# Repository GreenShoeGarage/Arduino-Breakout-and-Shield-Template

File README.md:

# Arduino MKR and UNO R4 breakout boards and prototyping shields

Seven PCB designs, including the UNO R4 Minima riser, from Green Shoe Garage cover two Arduino families. Each family includes a base board, a prototyping shield with a solder grid, and a blank shield for custom components. Each base board brings Arduino pins out to headers and 2.54 mm screw terminals. Both shield variants plug into the headers on their matching base board.

| Family | Base board | Prototyping shield | Blank workspace shield |
| --- | --- | --- | --- |
| Arduino MKR | [MKR Terminal Carrier](boards/mkr/terminal-carrier/) breaks out the two 14-pin rows, using the MKR WiFi 1010 as its reference. | [MKR Carrier ProtoShield](boards/mkr/protoshield/) has a 7 × 25 prototyping grid. Its underside sockets J1 and J2 mate with carrier headers J3 and J4, respectively. | [MKR Blank Shield](boards/mkr/blank-shield/) leaves the center open for component footprints and routing. It retains the two 14-pin underside sockets and two M3 mounting holes. |
| Arduino UNO R4 | [UNO R4 Bench Breakout](boards/uno-r4/bench-breakout/) Rev B picks up standard headers and ICSP, plus ESP, Qwiic and OFF/RTC on WiFi or SWD on Minima through a [rigid riser](boards/uno-r4/minima-swd-riser/). | [UNO R4 Companion Shield](boards/uno-r4/companion-shield/) has underside sockets for the breakout headers, labeled solder rows, and a 12 × 15 prototyping grid. | [UNO R4 Blank Shield](boards/uno-r4/blank-shield/) leaves the prototyping area open for component footprints and routing. It retains the nine underside socket banks and their labeled solder rows. |

## UNO R4 direct-stack revision B

[Assembly guide (PDF)](boards/uno-r4/bench-breakout/drawings/UNO-R4-Direct-Assembly.pdf) · [Variant BOM](boards/uno-r4/bench-breakout/Assembly-BOM.csv) · [Flux project ZIPs](boards/uno-r4/flux-import/)

The WiFi carrier uses two underside sockets and three spring probes. The Minima carrier uses a soldered SWD riser. Assemble one variant per carrier. Both upper shields receive signals through the existing nine male/female header pairs. The enclosure uses two precision locating spacers.

## Open a board

Download or clone the repository. In KiCad 9, open the `.kicad_pro` file in the chosen board directory, then launch the Schematic Editor or PCB Editor from the project window. Keep the whole directory together when copying a board or packaging it individually. The symbol and footprint tables resolve paths relative to the project.

Flux users can import an individual UNO project from the linked ZIP folder using **Import → Project**. Each ZIP contains one schematic and one routed layout. Live Flux import remains untested.

All three MKR projects and both UNO R4 shield projects include local STEP models. The UNO R4 Bench Breakout references the standard KiCad 9 model library through `KICAD9_3DMODEL_DIR` for its 3D view.

## View PCB files on GitHub

Gerber Viewer for GitHub adds an interactive preview above GitHub's file content. It supports this repository's native KiCad PCB and schematic files through the embedded KiCanvas viewer.

1. Install and enable the Chrome extension. [Gerber Viewer for GitHub](https://chromewebstore.google.com/detail/gerber-viewer-for-github/kjempphffigplmkbpjamikbfgpmdfbfn)
2. Open this repository on GitHub in that browser, then select a PCB or schematic link below to visit its file page.
3. Use the embedded viewer to zoom and pan. For PCB layouts, toggle layers to inspect copper routing, silkscreen, and the board outline.

For a new GitHub repository, upload or commit the extracted project folders so each PCB and schematic has its own file page.

| Board | PCB layout | Schematic |
| --- | --- | --- |
| MKR Terminal Carrier | [View PCB](boards/mkr/terminal-carrier/MKR-Terminal-Carrier.kicad_pcb) | [View schematic](boards/mkr/terminal-carrier/MKR-Terminal-Carrier.kicad_sch) |
| MKR Carrier ProtoShield | [View PCB](boards/mkr/protoshield/MKR-Carrier-ProtoShield.kicad_pcb) | [View schematic](boards/mkr/protoshield/MKR-Carrier-ProtoShield.kicad_sch) |
| MKR Blank Shield | [View PCB](boards/mkr/blank-shield/MKR-Blank-Shield.kicad_pcb) | [View schematic](boards/mkr/blank-shield/MKR-Blank-Shield.kicad_sch) |
| UNO R4 Bench Breakout | [View PCB](boards/uno-r4/bench-breakout/UNO-R4-Breakout.kicad_pcb) | [View schematic](boards/uno-r4/bench-breakout/UNO-R4-Breakout.kicad_sch) |
| UNO R4 Companion Shield | [View PCB](boards/uno-r4/companion-shield/UNO-R4-Companion-Shield.kicad_pcb) | [View schematic](boards/uno-r4/companion-shield/UNO-R4-Companion-Shield.kicad_sch) |
| UNO R4 Blank Shield | [View PCB](boards/uno-r4/blank-shield/UNO-R4-Blank-Shield.kicad_pcb) | [View schematic](boards/uno-r4/blank-shield/UNO-R4-Blank-Shield.kicad_sch) |
| UNO R4 Minima SWD riser | [View PCB](boards/uno-r4/minima-swd-riser/UNO-R4-SWD-Riser.kicad_pcb) | [View schematic](boards/uno-r4/minima-swd-riser/UNO-R4-SWD-Riser.kicad_sch) |

The extension also previews Gerber and Excellon drill files, folders containing Gerber layers, and ZIP archives containing Gerber layers committed to GitHub.

## Routing verification

The UNO R4 Rev B verification covers the new carrier, the Minima riser and both mating shields. The November 26 verification package covers the three MKR Rev A boards. The reports record digital routing, rule, and pin-mapping checks. Physical assemblies await bench measurement.

| Family | Verification report | Continuity checklist | Complete verification package |
| --- | --- | --- | --- |
| MKR | [Routing verification (PDF)](boards/mkr/verification/MKR-Routing-Verification.pdf) | [Pin continuity (CSV)](boards/mkr/verification/MKR-Pin-Continuity.csv) | [Reports, netlists, and audit](boards/mkr/verification/) |
| UNO R4 | [Routing verification](boards/uno-r4/verification/README.md) | [Pin continuity (CSV)](boards/uno-r4/verification/UNO-R4-Direct-Continuity.csv) | [Evidence, audited inputs, and replay scripts](boards/uno-r4/verification/) |

Each UNO R4 board directory contains Gerber and drill files under `fabrication/`. The UNO R4 verification directory includes a replay for the copper, drill and assembled pin mappings. The previous cable-based design is archived in [Rev A history](boards/uno-r4/history/UNO-R4-Rev-A.zip).

## Board gallery

The PCB images below were regenerated from the current KiCad files on November 27, 2026. Layouts show front copper in red and back copper in blue. Select a 3D view or PCB layout to open the full-size image.

### Arduino MKR

| Board | 3D view | PCB layout |
| --- | --- | --- |
| [MKR Terminal Carrier](boards/mkr/terminal-carrier/) |  |  |
| [MKR Carrier ProtoShield](boards/mkr/protoshield/) |  |  |
| [MKR Blank Shield](boards/mkr/blank-shield/) |  |  |

<details>
<summary>MKR Blank Shield layout with a 20 mm scale bar</summary>

</details>

### Arduino UNO R4

| Board | 3D view | PCB layout |
| --- | --- | --- |
| [UNO R4 Bench Breakout](boards/uno-r4/bench-breakout/) |  |  |
| [UNO R4 Companion Shield](boards/uno-r4/companion-shield/) |  |  |
| [UNO R4 Blank Shield](boards/uno-r4/blank-shield/) |  |  |
| [UNO R4 Minima SWD riser](boards/uno-r4/minima-swd-riser/) |  |  |

## Stack enclosures

Both enclosures accept the prototyping shield or blank shield for their matching board family. The dimensions below are nominal. Both designs await a physical fit test.

| MKR stack enclosure | UNO R4 stack enclosure |
| --- | --- |
|  |  |
| **98 × 130 × 37.2 mm.** Print the base and one lid. The access lid exposes the prototyping area. The covered lid shelters it. | **132 × 120 × 43 mm.** Use the base, open bezel, and two precision locators with the Rev B assembly. |
| [Printable STLs](enclosures/mkr/fabrication/) · [Assembly guide (PDF)](enclosures/mkr/drawings/MKR-Stack-Assembly-Guide.pdf) · [CAD and source](enclosures/mkr/) | [Printable STLs](enclosures/uno-r4/fabrication/) · [Assembly guide (PDF)](enclosures/uno-r4/drawings/UNO-R4-Stack-Assembly.pdf) · [CAD and source](enclosures/uno-r4/) |

## Source and licenses

The MKR and upper shield projects retain their original native design files. The Rev B carrier and Minima riser include editable KiCad projects and individual Flux-import ZIPs. The accompanying KiCad library license notices are included in their original locations.

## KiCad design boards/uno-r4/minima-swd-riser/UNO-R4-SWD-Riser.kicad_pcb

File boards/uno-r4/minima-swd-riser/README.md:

# UNO R4 Minima SWD riser · Rev B

Order one riser for each Minima carrier. Select the two-layer 1.6 mm PCB option. Riser J1 is a bottom-mounted 2 × 5 Harwin socket. Two soldered strips connect riser J2/J3 to carrier J19/J20. Install at a 4.60 mm board-to-board air gap. The pin-1 pad is square. Shield pad and terminal numbers are listed independently in the continuity table.

- [Assembly instructions](../bench-breakout/drawings/UNO-R4-Direct-Assembly.pdf)
- [Riser schematic](drawings/schematic.pdf)
- [Fabrication archive](UNO-R4-Minima-SWD-Riser-RevB-OSH-Park.zip)
- [Pin-by-pin checklist](../verification/UNO-R4-Direct-Continuity.csv)

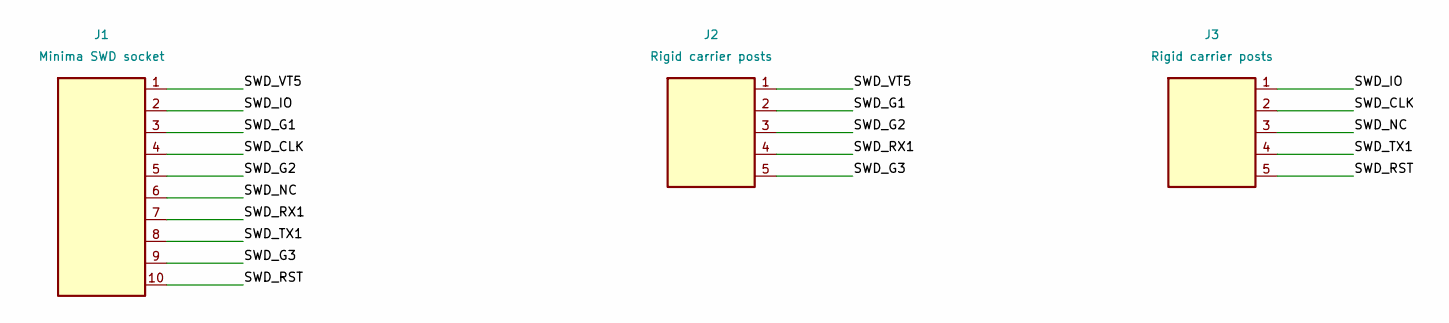
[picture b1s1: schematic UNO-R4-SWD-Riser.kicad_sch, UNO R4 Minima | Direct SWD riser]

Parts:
J1: Minima SWD socket; Harwin_M50-3000545; MPN M50-3000545
J2, J3: Rigid carrier posts; PinHeader_1x05_P2.54mm_Vertical; MPN TSW-105-07-G-S

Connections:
/SWD_CLK: J1.4, J3.2
/SWD_G1: J1.3, J2.2
/SWD_G2: J1.5, J2.3
/SWD_G3: J1.9, J2.5
/SWD_IO: J1.2, J3.1
/SWD_NC: J1.6, J3.3
/SWD_RST: J1.10, J3.5
/SWD_RX1: J1.7, J2.4
/SWD_TX1: J1.8, J3.4
/SWD_VT5: J1.1, J2.1

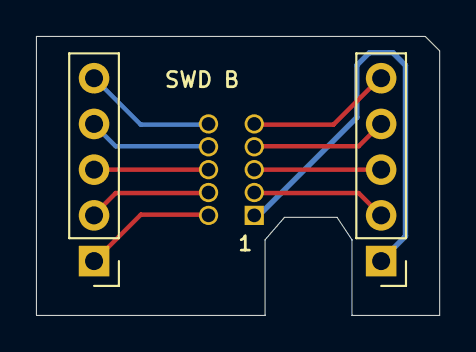
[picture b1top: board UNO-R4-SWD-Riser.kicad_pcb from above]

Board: 2 copper layers, 22.4 x 15.5 mm, 3 parts (1 on the bottom side), 10 nets.

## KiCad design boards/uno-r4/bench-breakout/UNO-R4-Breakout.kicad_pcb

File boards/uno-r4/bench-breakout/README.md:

# UNO R4 direct-stack breakout · Rev B

Select the underside hardware for the Arduino that will sit below the breakout. The four UNO edge header banks and ICSP mate directly on both models. ESP service, OFF/RTC and the dedicated Qwiic bus connect on WiFi. The rigid riser picks up the ten SWD connector positions on Minima. Either upper shield plugs into H1–H9.

- [Assembly guide and first-article checks](drawings/UNO-R4-Direct-Assembly.pdf)
- [Variant assembly BOM](Assembly-BOM.csv)
- [Every host contact, terminal and shield destination](pin-tables/Arduino-to-terminal.csv)
- [Electrical schematic](drawings/schematic.pdf)
- [Two-layer fabrication archive](UNO-R4-Direct-Breakout-RevB-OSH-Park.zip)
- [Minima riser](../minima-swd-riser/)
- [KiCad, Gerber and host contact verification](../verification/)

The two variants share the same PCB. Build one population per Arduino model. Leave the other model’s underside parts unpopulated and mark the build on the board. Model-specific banks without a matching host remain inactive. KiCad’s master view contains the alternate footprints. The carrier underside illustration shows the WiFi components. Generic connector 3D models illustrate placement. Use the MPNs and assembly dimensions for fabrication.

Import the individual zipped project from ../flux-import/ in Flux under **Import → Project**. The checked design of record is the included KiCad 9 project and its Gerbers. A live Flux import and a physical first article are pending.

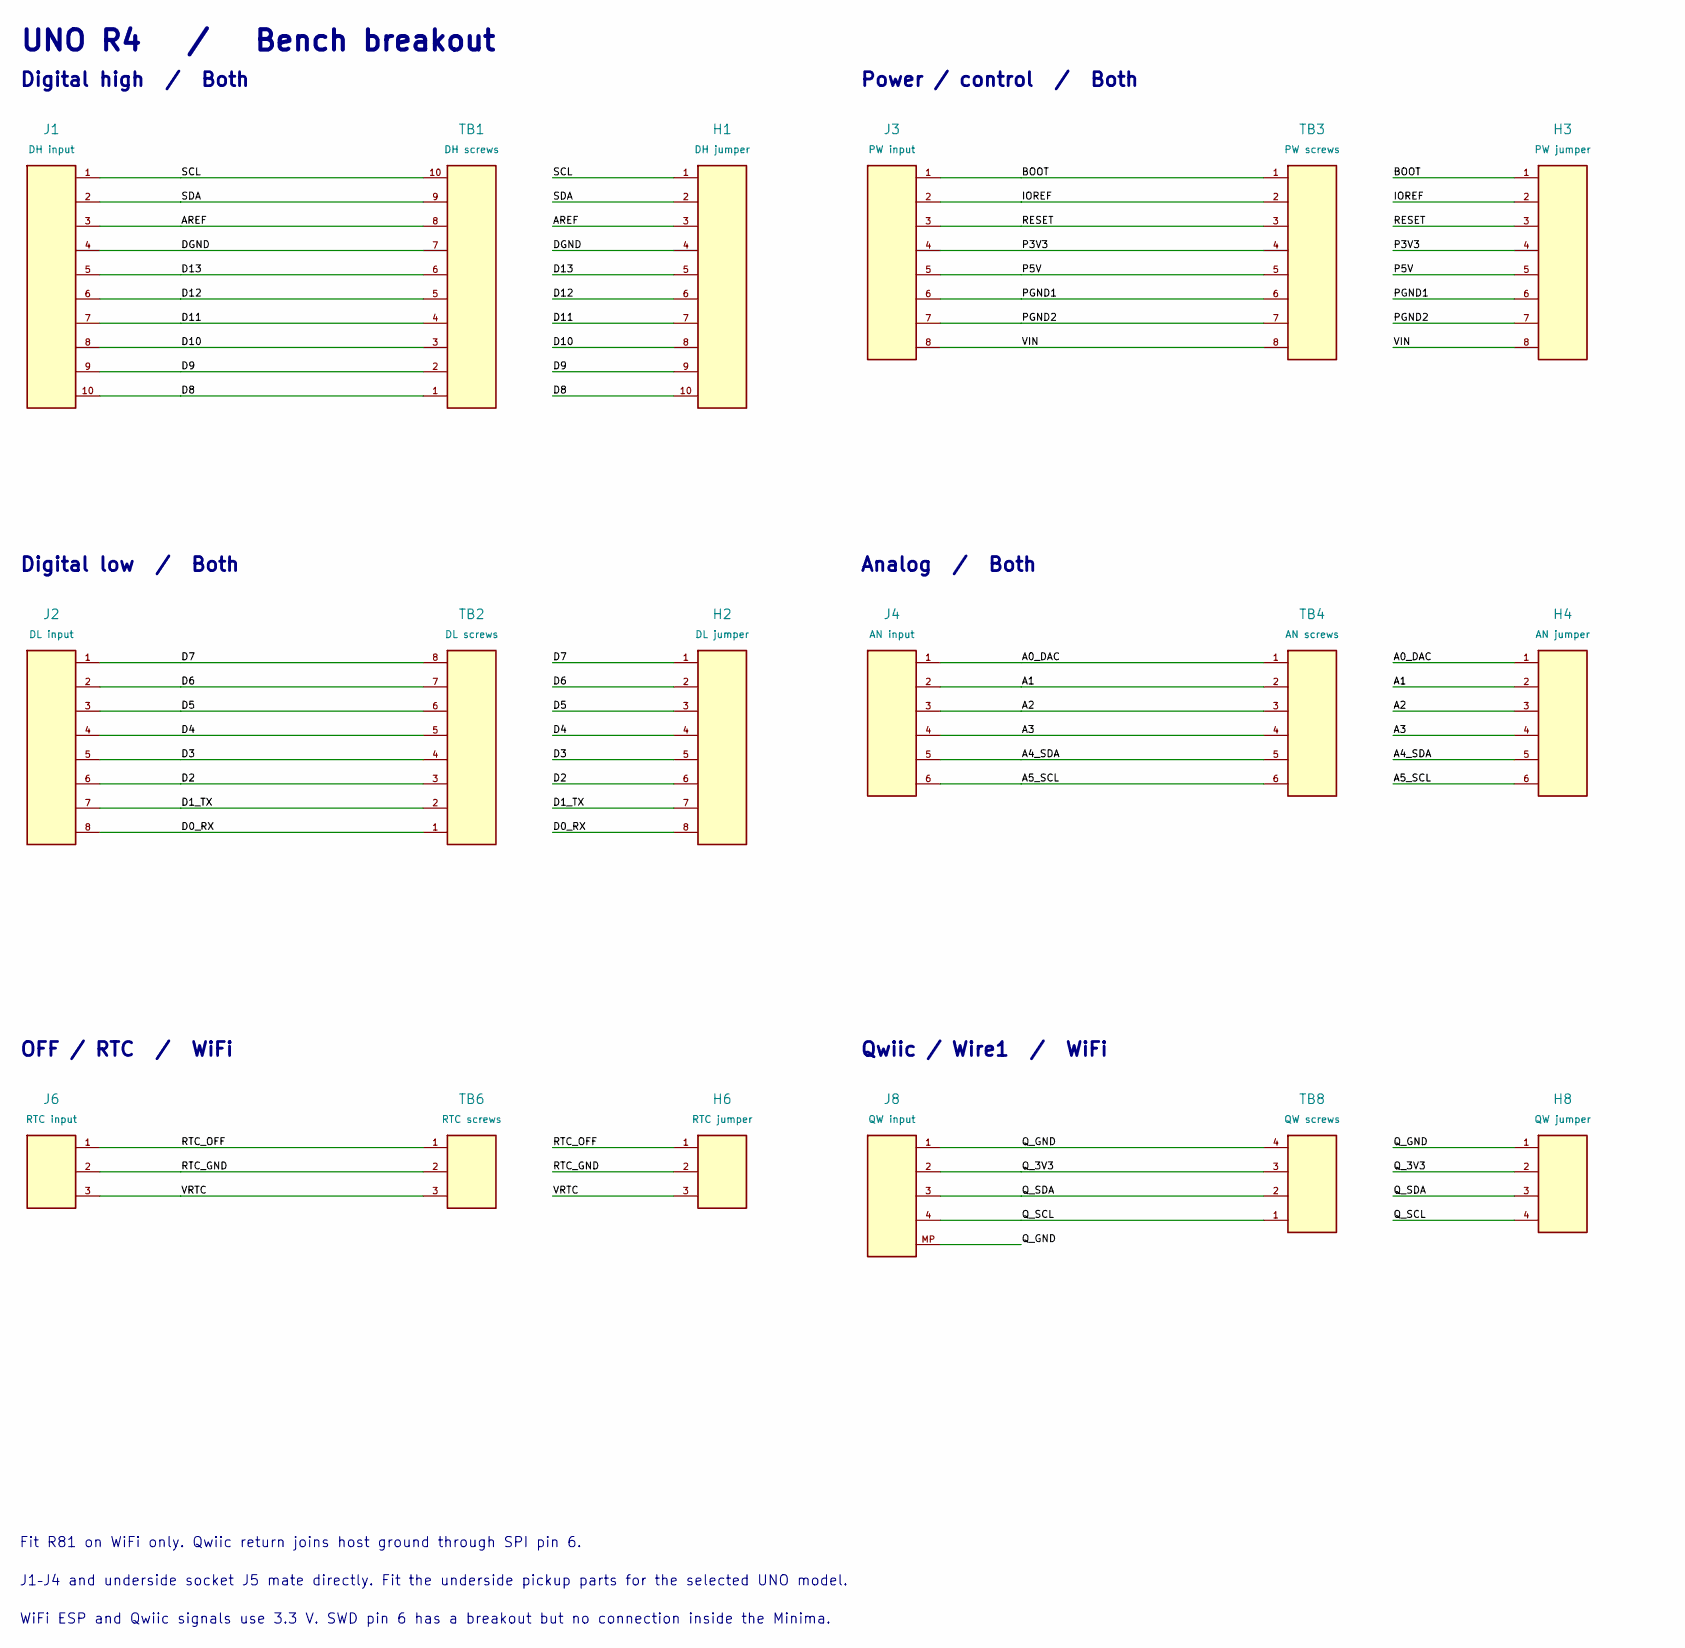
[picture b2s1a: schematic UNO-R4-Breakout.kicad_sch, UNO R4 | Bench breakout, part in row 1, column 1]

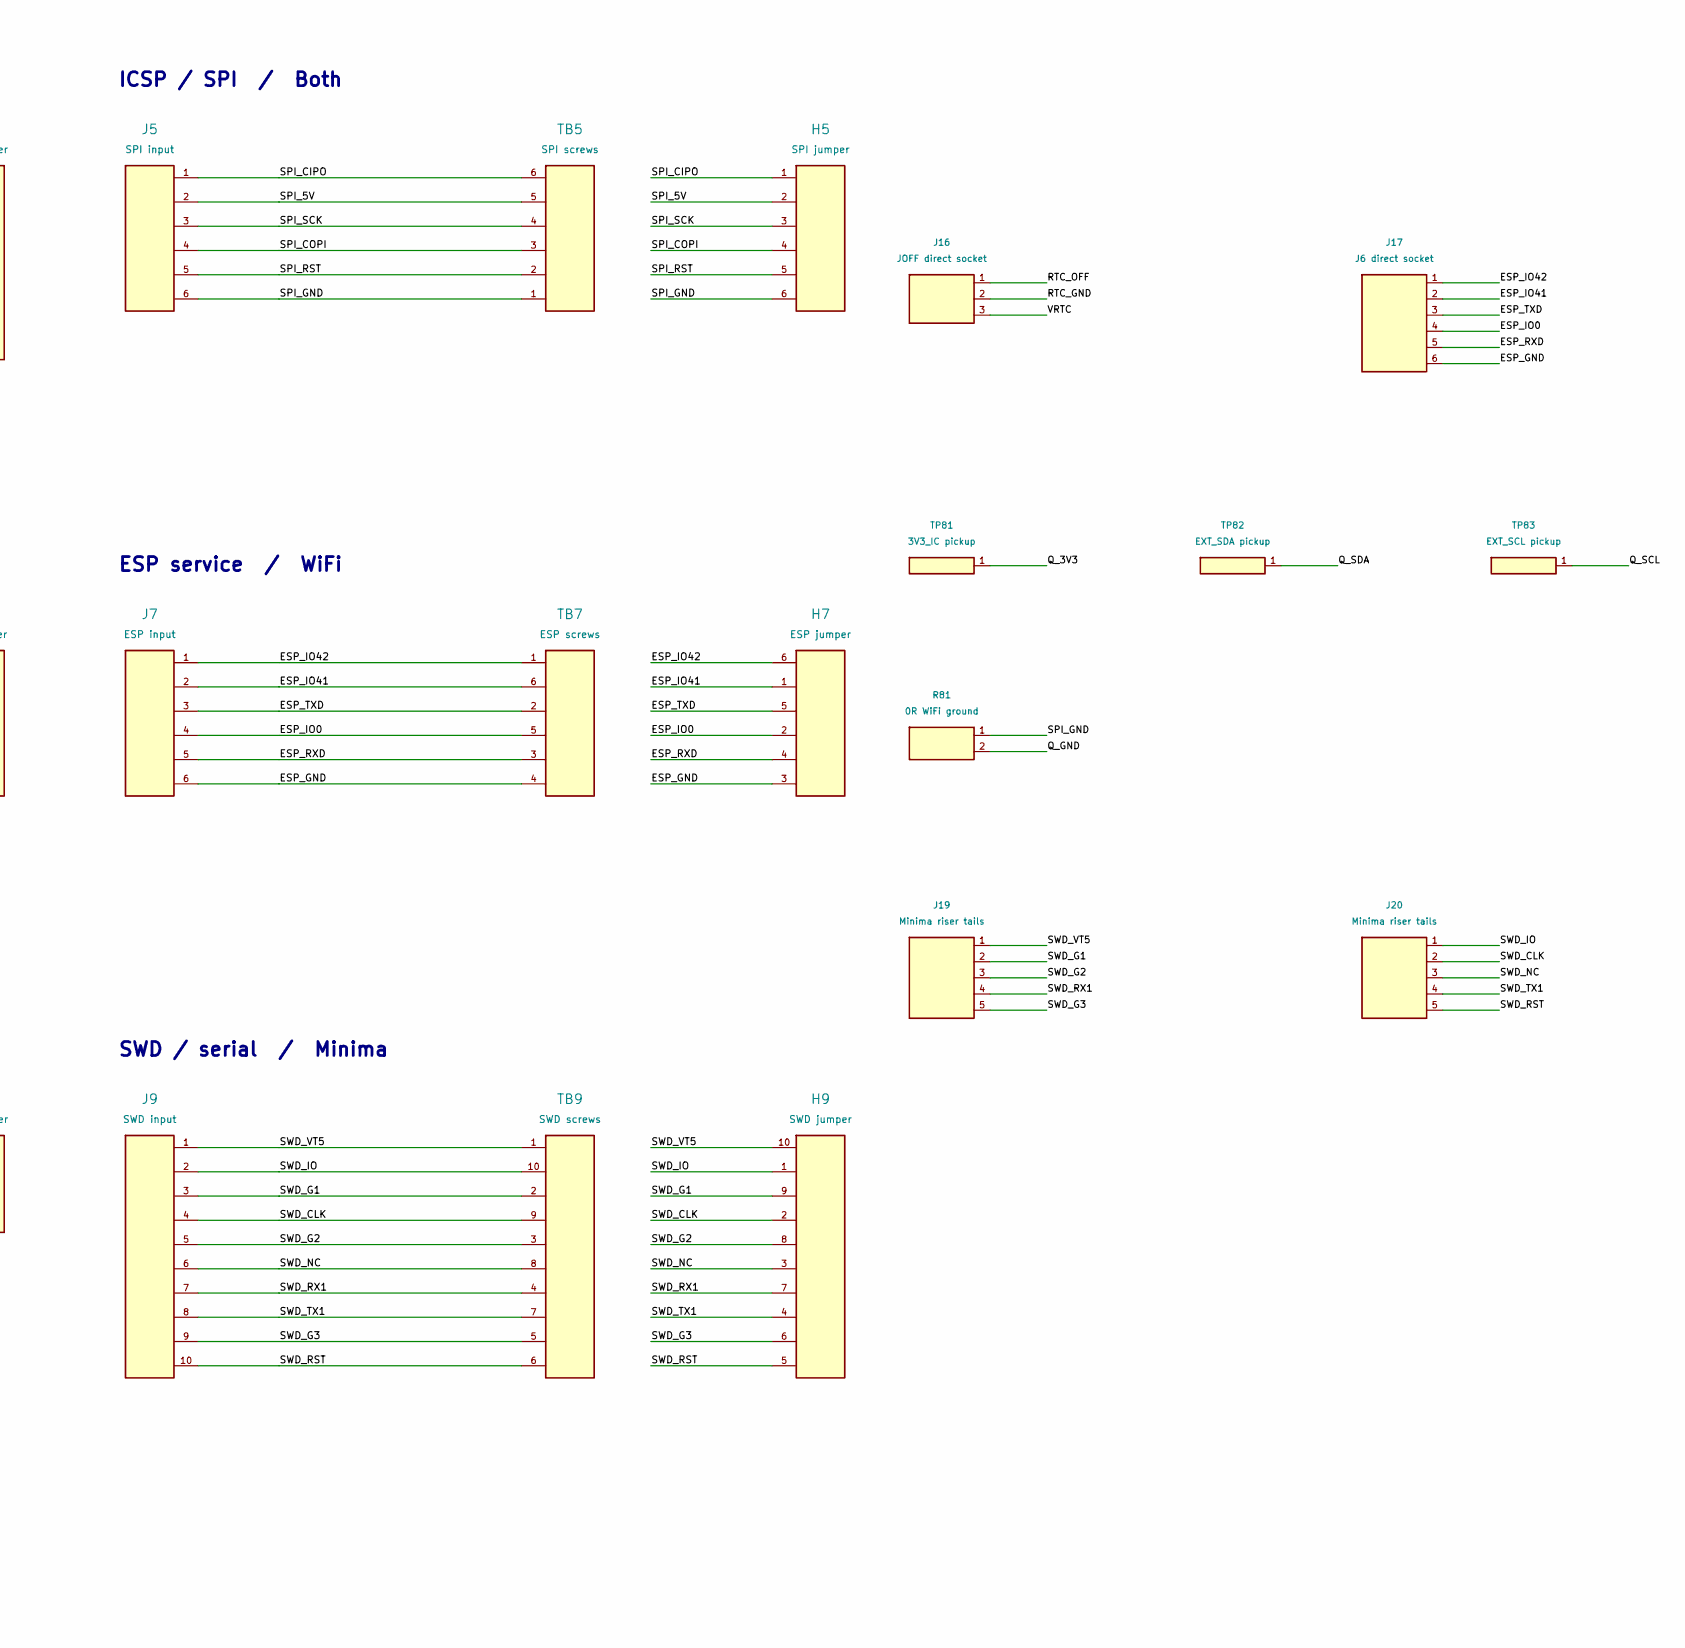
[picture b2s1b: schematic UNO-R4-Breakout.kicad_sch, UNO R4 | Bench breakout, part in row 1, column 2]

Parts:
H1: DH jumper; PinHeader_1x10_P2.54mm_Vertical; MPN TSW-110-07-G-S
H2: DL jumper; PinHeader_1x08_P2.54mm_Vertical; MPN TSW-108-07-G-S
H3: PW jumper; PinHeader_1x08_P2.54mm_Vertical; MPN TSW-108-07-G-S
H4: AN jumper; PinHeader_1x06_P2.54mm_Vertical; MPN TSW-106-07-G-S
H5: SPI jumper; PinHeader_1x06_P2.54mm_Vertical; MPN TSW-106-07-G-S
H6: RTC jumper; PinHeader_1x03_P2.54mm_Vertical; MPN TSW-103-07-G-S
H7: ESP jumper; PinHeader_1x06_P2.54mm_Vertical; MPN TSW-106-07-G-S
H8: QW jumper; PinHeader_1x04_P2.54mm_Vertical; MPN TSW-104-07-G-S
H9: SWD jumper; PinHeader_1x10_P2.54mm_Vertical; MPN TSW-110-07-G-S
J1: DH input; PinSocket_1x10_P2.54mm_Vertical; MPN PRT-11417 [10]
J2: DL input; PinSocket_1x08_P2.54mm_Vertical; MPN PRT-11417 [8]
J3: PW input; PinSocket_1x08_P2.54mm_Vertical; MPN PRT-11417 [8]
J4: AN input; PinSocket_1x06_P2.54mm_Vertical; MPN PRT-11417 [6]
J5: SPI input; PinSocket_2x03_P2.54mm_Vertical; MPN SSW-103-01-G-D
J6: RTC input; PinHeader_1x03_P2.54mm_Vertical; MPN TSW-103-07-G-S
J7: ESP input; PinHeader_2x03_P2.54mm_Vertical; MPN TSW-103-07-G-D
J8: QW input; JST_SH_BM04B-SRSS-TB_1x04-1MP_P1.00mm_Vertical; MPN BM04B-SRSS-TB(LF)(SN)
J9: SWD input; Samtec_FTSH-105-01-L-D; MPN FTSH-105-01-L-D
J16: JOFF direct socket; PinSocket_1x03_P2.54mm_Vertical; MPN SSW-103-01-G-S
J17: J6 direct socket; PinSocket_2x03_P2.54mm_Vertical; MPN SSW-103-01-G-D
J19, J20: Minima riser tails; Riser_Tails_1x05; MPN TSW-105-07-G-S • shared with riser
R81: 0R WiFi ground; R_0805_2012Metric; MPN RC0805JR-070RL
TB1: DH screws; TerminalBlock_Phoenix_MPT-0,5-10-2.54_1x10_P2.54mm_Horizont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; MPN 1725737
TB2: DL screws; TerminalBlock_Phoenix_MPT-0,5-8-2.54_1x08_P2.54mm_Horizontal; MPN 1725711
TB3: PW screws; TerminalBlock_Phoenix_MPT-0,5-8-2.54_1x08_P2.54mm_Horizontal; MPN 1725711
TB4: AN screws; TerminalBlock_Phoenix_MPT-0,5-6-2.54_1x06_P2.54mm_Horizontal; MPN 1725698
TB5: SPI screws; TerminalBlock_Phoenix_MPT-0,5-6-2.54_1x06_P2.54mm_Horizontal; MPN 1725698
TB6: RTC screws; TerminalBlock_Phoenix_MPT-0,5-3-2.54_1x03_P2.54mm_Horizontal; MPN 1725669
TB7: ESP screws; TerminalBlock_Phoenix_MPT-0,5-6-2.54_1x06_P2.54mm_Horizontal; MPN 1725698
TB8: QW screws; TerminalBlock_Phoenix_MPT-0,5-4-2.54_1x04_P2.54mm_Horizontal; MPN 1725672
TB9: SWD screws; TerminalBlock_Phoenix_MPT-0,5-10-2.54_1x10_P2.54mm_Horizont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; MPN 1725737
TP81: 3V3_IC pickup; Probe_S13; MPN S13-503 + P13-0123
TP82: EXT_SDA pickup; Probe_S13; MPN S13-503 + P13-0123
TP83: EXT_SCL pickup; Probe_S13; MPN S13-503 + P13-0123

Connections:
/A0_DAC: H4.1, J4.1, TB4.1
/A1: H4.2, J4.2, TB4.2
/A2: H4.3, J4.3, TB4.3
/A3: H4.4, J4.4, TB4.4
/A4_SDA: H4.5, J4.5, TB4.5
/A5_SCL: H4.6, J4.6, TB4.6
/AREF: H1.3, J1.3, TB1.8
/BOOT: H3.1, J3.1, TB3.1
/D0_RX: H2.8, J2.8, TB2.1
/D1_TX: H2.7, J2.7, TB2.2
/D2: H2.6, J2.6, TB2.3
/D3: H2.5, J2.5, TB2.4
/D4: H2.4, J2.4, TB2.5
/D5: H2.3, J2.3, TB2.6
/D6: H2.2, J2.2, TB2.7
/D7: H2.1, J2.1, TB2.8
/D8: H1.10, J1.10, TB1.1
/D9: H1.9, J1.9, TB1.2
/D10: H1.8, J1.8, TB1.3
/D11: H1.7, J1.7, TB1.4
/D12: H1.6, J1.6, TB1.5
/D13: H1.5, J1.5, TB1.6
/DGND: H1.4, J1.4, TB1.7
/ESP_GND: H7.3, J7.6, J17.6, TB7.4
/ESP_IO0: H7.2, J7.4, J17.4, TB7.5
/ESP_IO41: H7.1, J7.2, J17.2, TB7.6
/ESP_IO42: H7.6, J7.1, J17.1, TB7.1
/ESP_RXD: H7.4, J7.5, J17.5, TB7.3
/ESP_TXD: H7.5, J7.3, J17.3, TB7.2
/IOREF: H3.2, J3.2, TB3.2
/P3V3: H3.4, J3.4, TB3.4
/P5V: H3.5, J3.5, TB3.5
/PGND1: H3.6, J3.6, TB3.6
/PGND2: H3.7, J3.7, TB3.7
/Q_3V3: H8.2, J8.2, TB8.3, TP81.1
/Q_GND: H8.1, J8.1, J8.MP, R81.2, TB8.4
/Q_SCL: H8.4, J8.4, TB8.1, TP83.1
/Q_SDA: H8.3, J8.3, TB8.2, TP82.1
/RESET: H3.3, J3.3, TB3.3
/RTC_GND: H6.2, J6.2, J16.2, TB6.2
/RTC_OFF: H6.1, J6.1, J16.1, TB6.1
/SCL: H1.1, J1.1, TB1.10
/SDA: H1.2, J1.2, TB1.9
/SPI_5V: H5.2, J5.2, TB5.5
/SPI_CIPO: H5.1, J5.1, TB5.6
/SPI_COPI: H5.4, J5.4, TB5.3
/SPI_GND: H5.6, J5.6, R81.1, TB5.1
/SPI_RST: H5.5, J5.5, TB5.2
/SPI_SCK: H5.3, J5.3, TB5.4
/SWD_CLK: H9.2, J9.4, J20.2, TB9.9
/SWD_G1: H9.9, J9.3, J19.2, TB9.2
/SWD_G2: H9.8, J9.5, J19.3, TB9.3
/SWD_G3: H9.6, J9.9, J19.5, TB9.5
/SWD_IO: H9.1, J9.2, J20.1, TB9.10
/SWD_NC: H9.3, J9.6, J20.3, TB9.8
/SWD_RST: H9.5, J9.10, J20.5, TB9.6
/SWD_RX1: H9.7, J9.7, J19.4, TB9.4
/SWD_TX1: H9.4, J9.8, J20.4, TB9.7
/SWD_VT5: H9.10, J9.1, J19.1, TB9.1
/VIN: H3.8, J3.8, TB3.8
/VRTC: H6.3, J6.3, J16.3, TB6.3

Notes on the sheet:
Digital high / Both
Power / control / Both
ICSP / SPI / Both
Digital low / Both
Analog / Both
ESP service / WiFi
OFF / RTC / WiFi
Qwiic / Wire1 / WiFi
SWD / serial / Minima
UNO R4 / Bench breakout
Fit R81 on WiFi only. Qwiic return joins host ground through SPI pin 6.
J1–J4 and underside socket J5 mate directly. Fit the underside pickup parts for the selected UNO model.
WiFi ESP and Qwiic signals use 3.3 V. SWD pin 6 has a breakout but no connection inside the Minima.

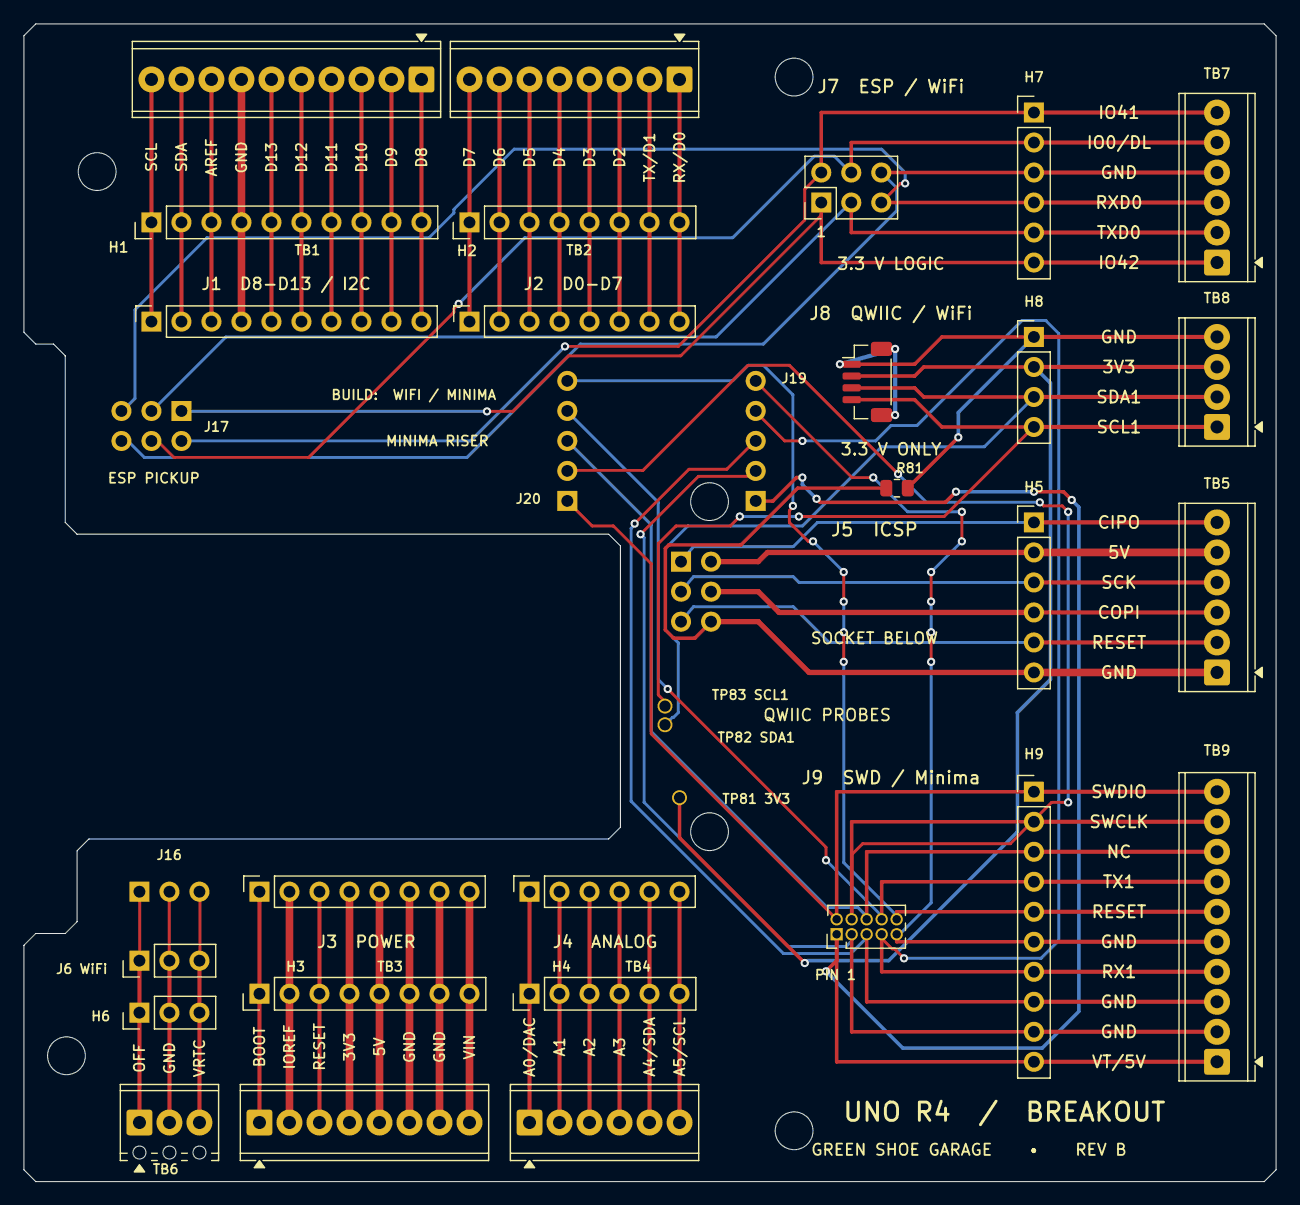
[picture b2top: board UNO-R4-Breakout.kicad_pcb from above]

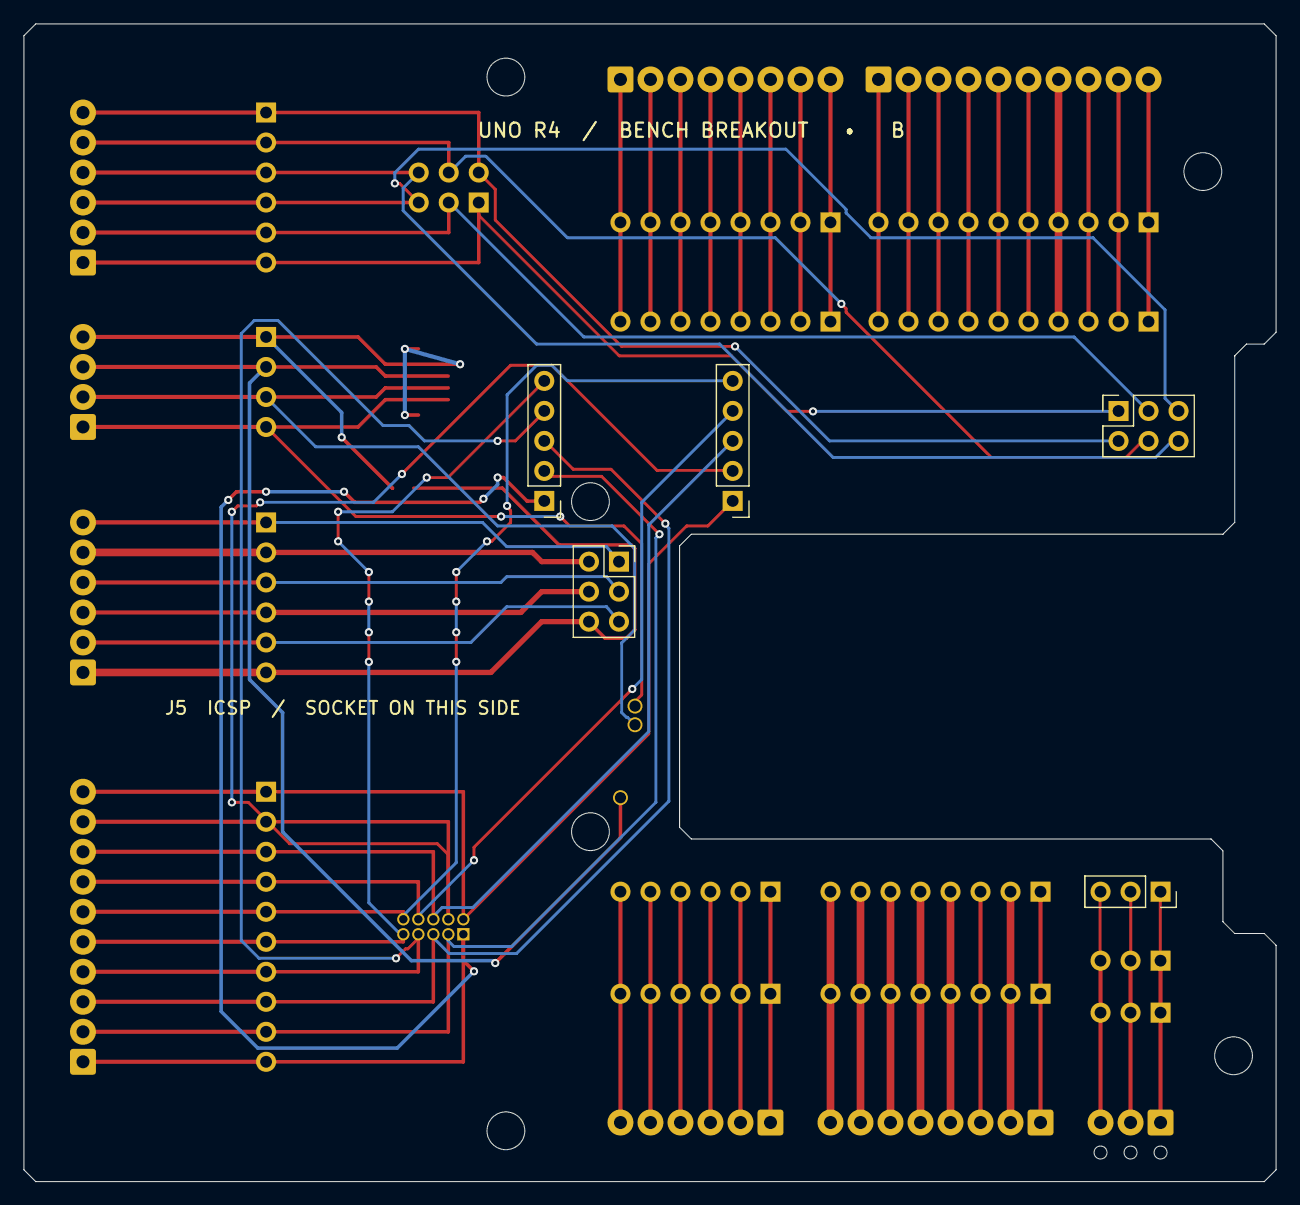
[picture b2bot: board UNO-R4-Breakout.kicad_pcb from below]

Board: 2 copper layers, 106.0 x 98.0 mm, 41 parts (8 on the bottom side), 61 nets.

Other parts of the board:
MH1, MH2, MH3, MH4: 3.2 mm; MountingHole_3.2mm_M3
MH5, MH6: 3.20 mm guide; Guide_3.20

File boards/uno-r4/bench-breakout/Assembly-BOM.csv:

Assembly,Reference,WiFi quantity,Minima quantity,Side,Manufacturer,Orderable part or item,Installation
Carrier,J1,1,1,Top,SparkFun,PRT-11417 [10],Long tails toward Arduino; purchase one kit for J1–J4
Carrier,H1,1,1,Top,Samtec,TSW-110-07-G-S,Male header to upper shield
Carrier,TB1,1,1,Top,Phoenix Contact,1725737,2.54 mm screw terminal
Carrier,J2,1,1,Top,SparkFun,PRT-11417 [8],Long tails toward Arduino; purchase one kit for J1–J4
Carrier,H2,1,1,Top,Samtec,TSW-108-07-G-S,Male header to upper shield
Carrier,TB2,1,1,Top,Phoenix Contact,1725711,2.54 mm screw terminal
Carrier,J3,1,1,Top,SparkFun,PRT-11417 [8],Long tails toward Arduino; purchase one kit for J1–J4
Carrier,H3,1,1,Top,Samtec,TSW-108-07-G-S,Male header to upper shield
Carrier,TB3,1,1,Top,Phoenix Contact,1725711,2.54 mm screw terminal
Carrier,J4,1,1,Top,SparkFun,PRT-11417 [6],Long tails toward Arduino; purchase one kit for J1–J4
Carrier,H4,1,1,Top,Samtec,TSW-106-07-G-S,Male header to upper shield
Carrier,TB4,1,1,Top,Phoenix Contact,1725698,2.54 mm screw terminal
Carrier,J5,1,1,Bottom,Samtec,SSW-103-01-G-D,Female socket faces Arduino
Carrier,H5,1,1,Top,Samtec,TSW-106-07-G-S,Male header to upper shield
Carrier,TB5,1,1,Top,Phoenix Contact,1725698,2.54 mm screw terminal
Carrier,J6,optional,—,Top,Samtec,TSW-103-07-G-S,Optional duplicate top service connector
Carrier,H6,1,1,Top,Samtec,TSW-103-07-G-S,Male header to upper shield
Carrier,TB6,1,1,Top,Phoenix Contact,1725669,2.54 mm screw terminal
Carrier,J7,optional,—,Top,Samtec,TSW-103-07-G-D,Optional duplicate top service connector
Carrier,H7,1,1,Top,Samtec,TSW-106-07-G-S,Male header to upper shield
Carrier,TB7,1,1,Top,Phoenix Contact,1725698,2.54 mm screw terminal
Carrier,J8,optional,—,Top,JST,BM04B-SRSS-TB(LF)(SN),Optional duplicate top service connector
Carrier,H8,1,1,Top,Samtec,TSW-104-07-G-S,Male header to upper shield
Carrier,TB8,1,1,Top,Phoenix Contact,1725672,2.54 mm screw terminal
Carrier,J9,—,optional,Top,Samtec,FTSH-105-01-L-D,Optional duplicate top service connector
Carrier,H9,1,1,Top,Samtec,TSW-110-07-G-S,Male header to upper shield
Carrier,TB9,1,1,Top,Phoenix Contact,1725737,2.54 mm screw terminal
Carrier,J16,1,—,Bottom,Samtec,SSW-103-01-G-S,WiFi JOFF socket
Carrier,J17,1,—,Bottom,Samtec,SSW-103-01-G-D,WiFi ESP socket
Carrier,TP81–TP83,3,—,Bottom,Harwin,S13-503,Solder sleeves. Install under a height fixture
Carrier,TP81–TP83,3,—,Bottom,Harwin,P13-0123,"Replaceable spring probes, 13.35 mm free projection"
Carrier,R81,1,—,Top,Yageo,RC0805JR-070RL,0 ohm 0805 Qwiic return link
Carrier + riser,"J19/J20 on carrier, J2/J3 on riser",—,2,Between boards,Samtec,TSW-105-07-G-S,Two strips total. Solder each to both boards
Riser,J1,—,1,Bottom,Harwin,M50-3000545,Minima J2 SWD mating socket
Stack,MH5,1,1,Between Arduino and carrier,Green Shoe Garage,Locating-Spacer-Round,Insulating acetal or dimensionally verified finished print
Stack,MH6,1,1,Between Arduino and carrier,Green Shoe Garage,Locating-Spacer-Diamond,Relief along hole-to-hole axis
Stack,MH5/MH6,2,2,Guide screws,Metric,M2 x 24 mm in enclosure,Free-standing assembly uses M2 x 18 mm with nuts

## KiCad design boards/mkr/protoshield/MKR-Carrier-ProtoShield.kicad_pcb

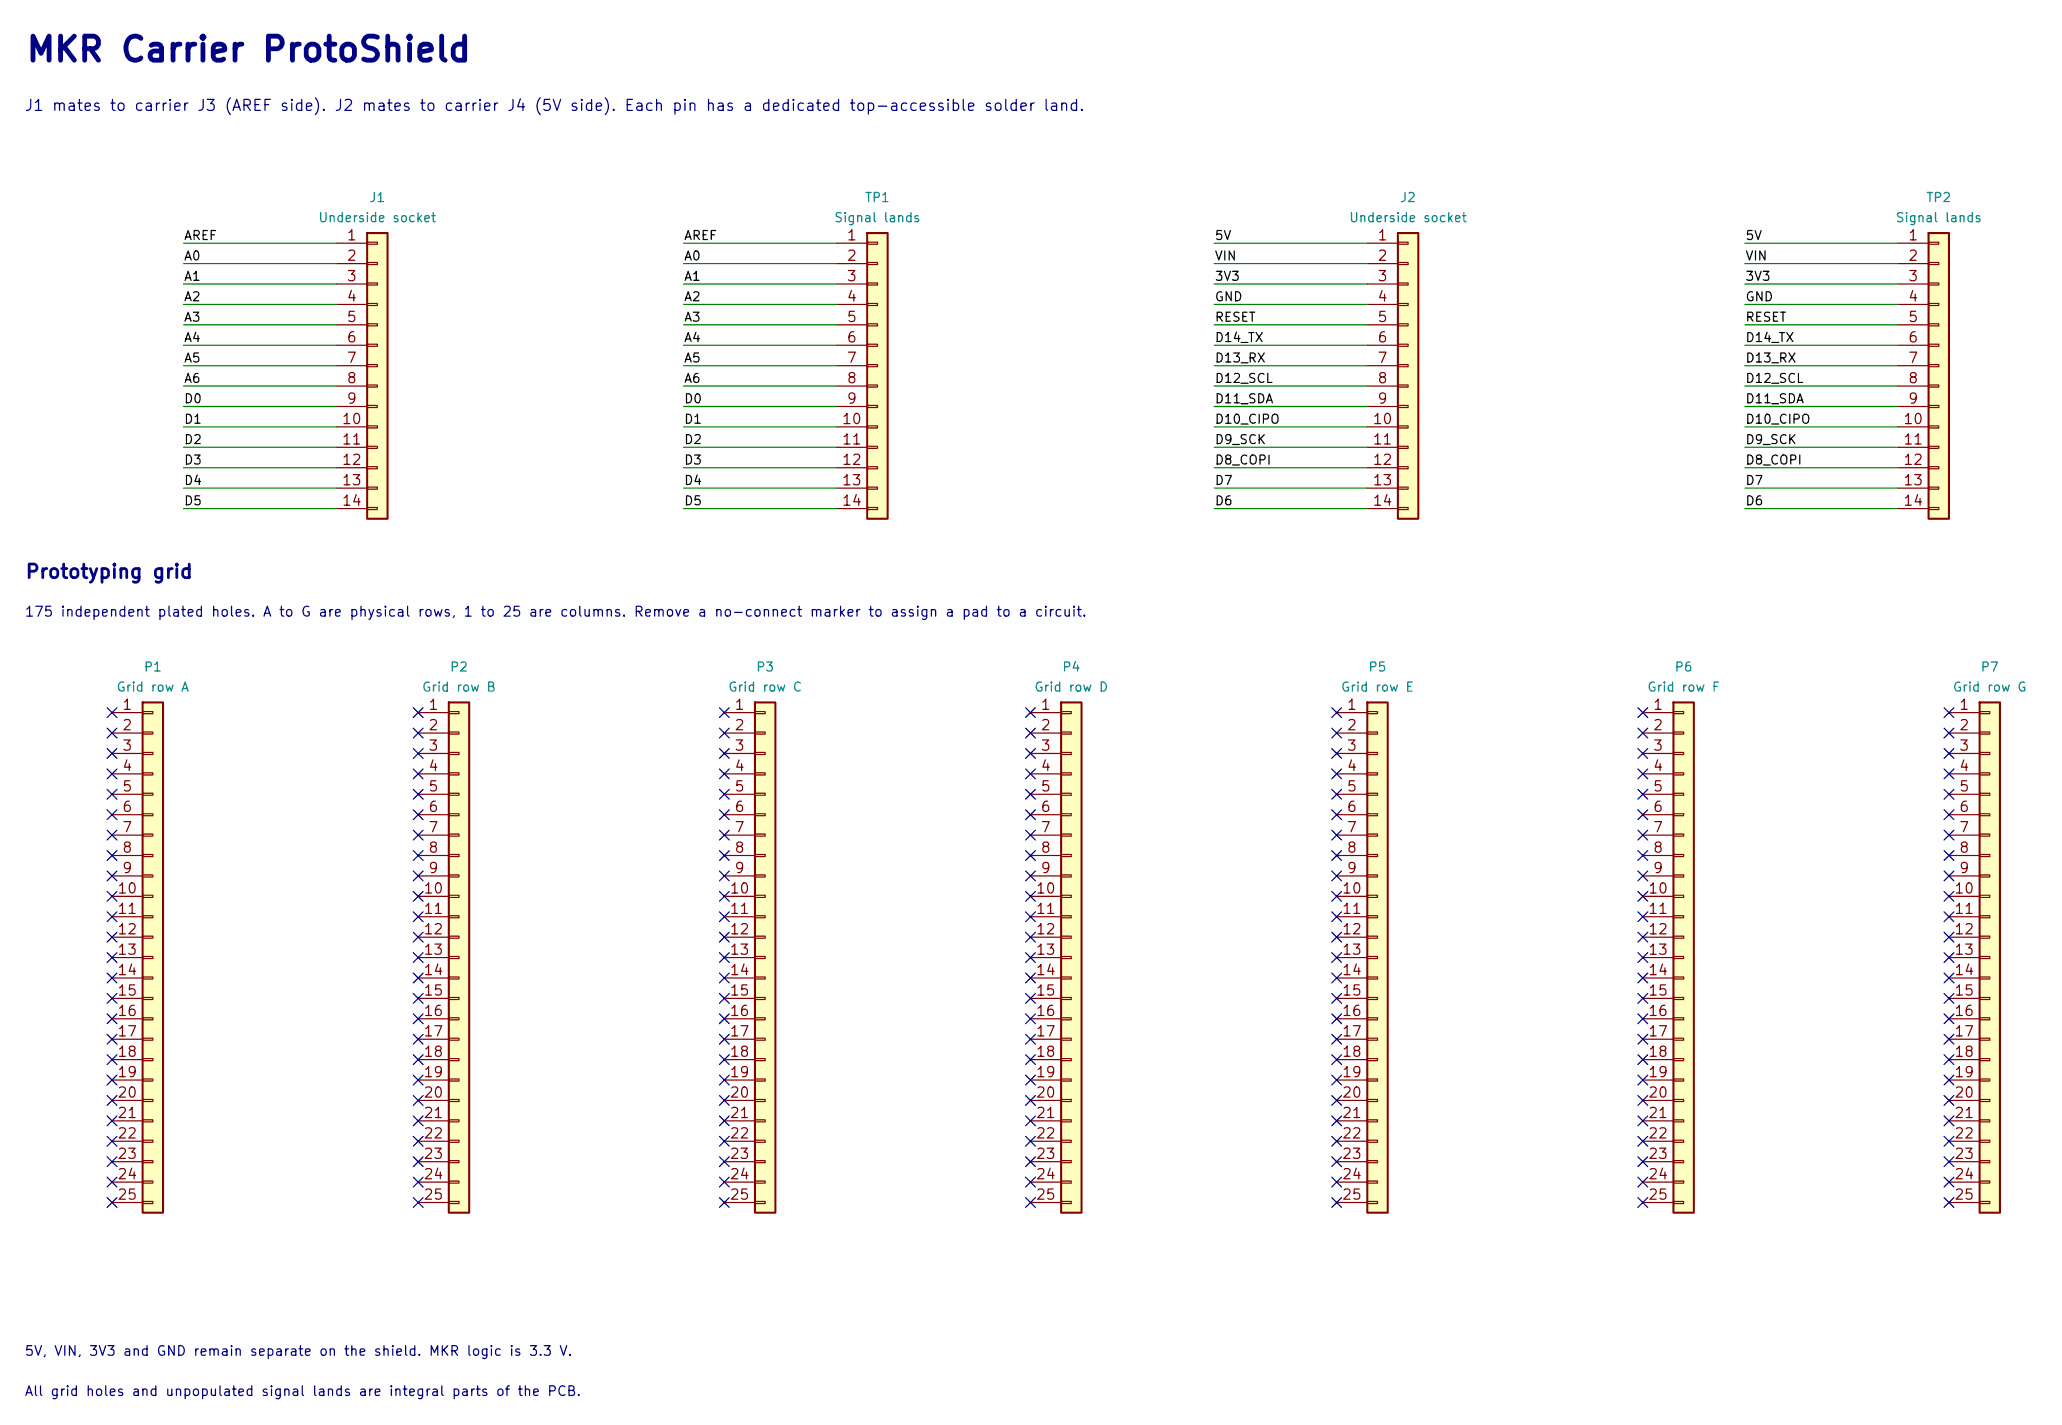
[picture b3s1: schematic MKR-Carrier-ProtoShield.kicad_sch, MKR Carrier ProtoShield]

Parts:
J1, J2: Underside socket; PinSocket_1x14_P2.54mm_Vertical; MPN SSW-114-01-G-S
P1: Grid row A; Proto_Row_1x25_P2.54mm
P2: Grid row B; Proto_Row_1x25_P2.54mm
P3: Grid row C; Proto_Row_1x25_P2.54mm
P4: Grid row D; Proto_Row_1x25_P2.54mm
P5: Grid row E; Proto_Row_1x25_P2.54mm
P6: Grid row F; Proto_Row_1x25_P2.54mm
P7: Grid row G; Proto_Row_1x25_P2.54mm
TP1, TP2: Signal lands; Solder_Lands_1x14_P2.54mm

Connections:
/3V3: J2.3, TP2.3
/5V: J2.1, TP2.1
/A0: J1.2, TP1.2
/A1: J1.3, TP1.3
/A2: J1.4, TP1.4
/A3: J1.5, TP1.5
/A4: J1.6, TP1.6
/A5: J1.7, TP1.7
/A6: J1.8, TP1.8
/AREF: J1.1, TP1.1
/D0: J1.9, TP1.9
/D1: J1.10, TP1.10
/D2: J1.11, TP1.11
/D3: J1.12, TP1.12
/D4: J1.13, TP1.13
/D5: J1.14, TP1.14
/D6: J2.14, TP2.14
/D7: J2.13, TP2.13
/D8_COPI: J2.12, TP2.12
/D9_SCK: J2.11, TP2.11
/D10_CIPO: J2.10, TP2.10
/D11_SDA: J2.9, TP2.9
/D12_SCL: J2.8, TP2.8
/D13_RX: J2.7, TP2.7
/D14_TX: J2.6, TP2.6
/GND: J2.4, TP2.4
/RESET: J2.5, TP2.5
/VIN: J2.2, TP2.2

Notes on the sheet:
MKR Carrier ProtoShield
J1 mates to carrier J3 (AREF side). J2 mates to carrier J4 (5V side). Each pin has a dedicated top-accessible solder land.
Prototyping grid
175 independent plated holes. A to G are physical rows, 1 to 25 are columns. Remove a no-connect marker to assign a pad to a circuit.
5V, VIN, 3V3 and GND remain separate on the shield. MKR logic is 3.3 V.
All grid holes and unpopulated signal lands are integral parts of the PCB.
